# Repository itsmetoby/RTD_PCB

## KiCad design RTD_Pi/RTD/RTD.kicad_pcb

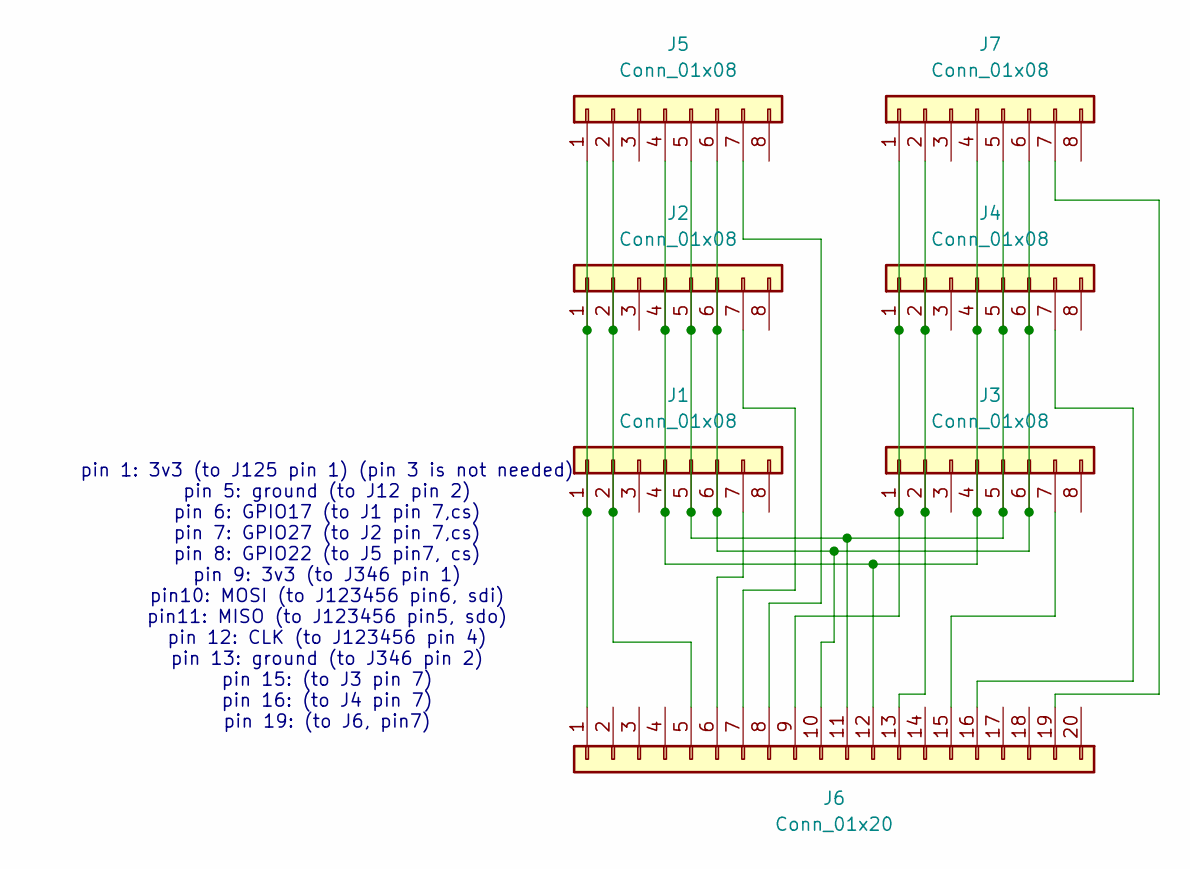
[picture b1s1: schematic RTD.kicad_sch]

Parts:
J1, J2, J3, J4, J5, J7: Conn_01x08; PinHeader_1x08_P2.54mm_Vertical
J6: Conn_01x20; PinHeader_1x20_P2.54mm_Vertical

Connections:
unnamed: J1.1, J2.1, J5.1, J6.1 (Pin_20)
unnamed: J1.2, J2.2, J5.2, J6.5 (Pin_16)
unnamed: J1.4, J2.4, J3.4, J4.4, J5.4, J6.12 (Pin_9), J7.4
unnamed: J1.5, J2.5, J3.5, J4.5, J5.5, J6.11 (Pin_10), J7.5
unnamed: J1.6, J2.6, J3.6, J4.6, J5.6, J6.10 (Pin_11), J7.6
unnamed: J1.7, J6.6 (Pin_15)
unnamed: J2.7, J6.7 (Pin_14)
unnamed: J3.1, J4.1, J6.9 (Pin_12), J7.1
unnamed: J3.2, J4.2, J6.13 (Pin_8), J7.2
unnamed: J3.7, J6.15 (Pin_6)
unnamed: J4.7, J6.16 (Pin_5)
unnamed: J5.7, J6.8
unnamed: J6.19 (Pin_2), J7.7

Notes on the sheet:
pin 1: 3v3 (to J125 pin 1) (pin 3 is not needed) pin 5: ground (to J12 pin 2) pin 6: GPIO17 (to J1 pin 7,cs) pin 7: GPIO27 (to J2 pin 7,cs) pin 8: GPIO22 (to J5 pin7, cs) pin 9: 3v3 (to J346 pin 1) pin10: MOSI (to J123456 pin6, sdi) pin11: MISO (to J123456 pin5, sdo) pin 12: CLK (to J123456 pin 4) 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

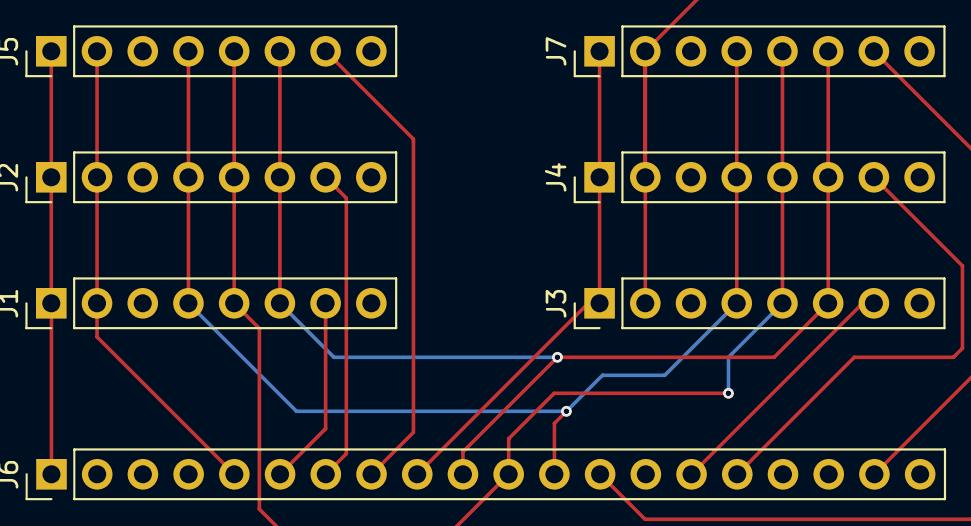
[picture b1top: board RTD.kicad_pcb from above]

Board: 2 copper layers, 7 parts (0 on the bottom side), 13 nets.

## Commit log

2025-05-07 Some update
2025-05-07 Create emtpy
2025-05-07 Add files via upload
    version 1 of PCB design
